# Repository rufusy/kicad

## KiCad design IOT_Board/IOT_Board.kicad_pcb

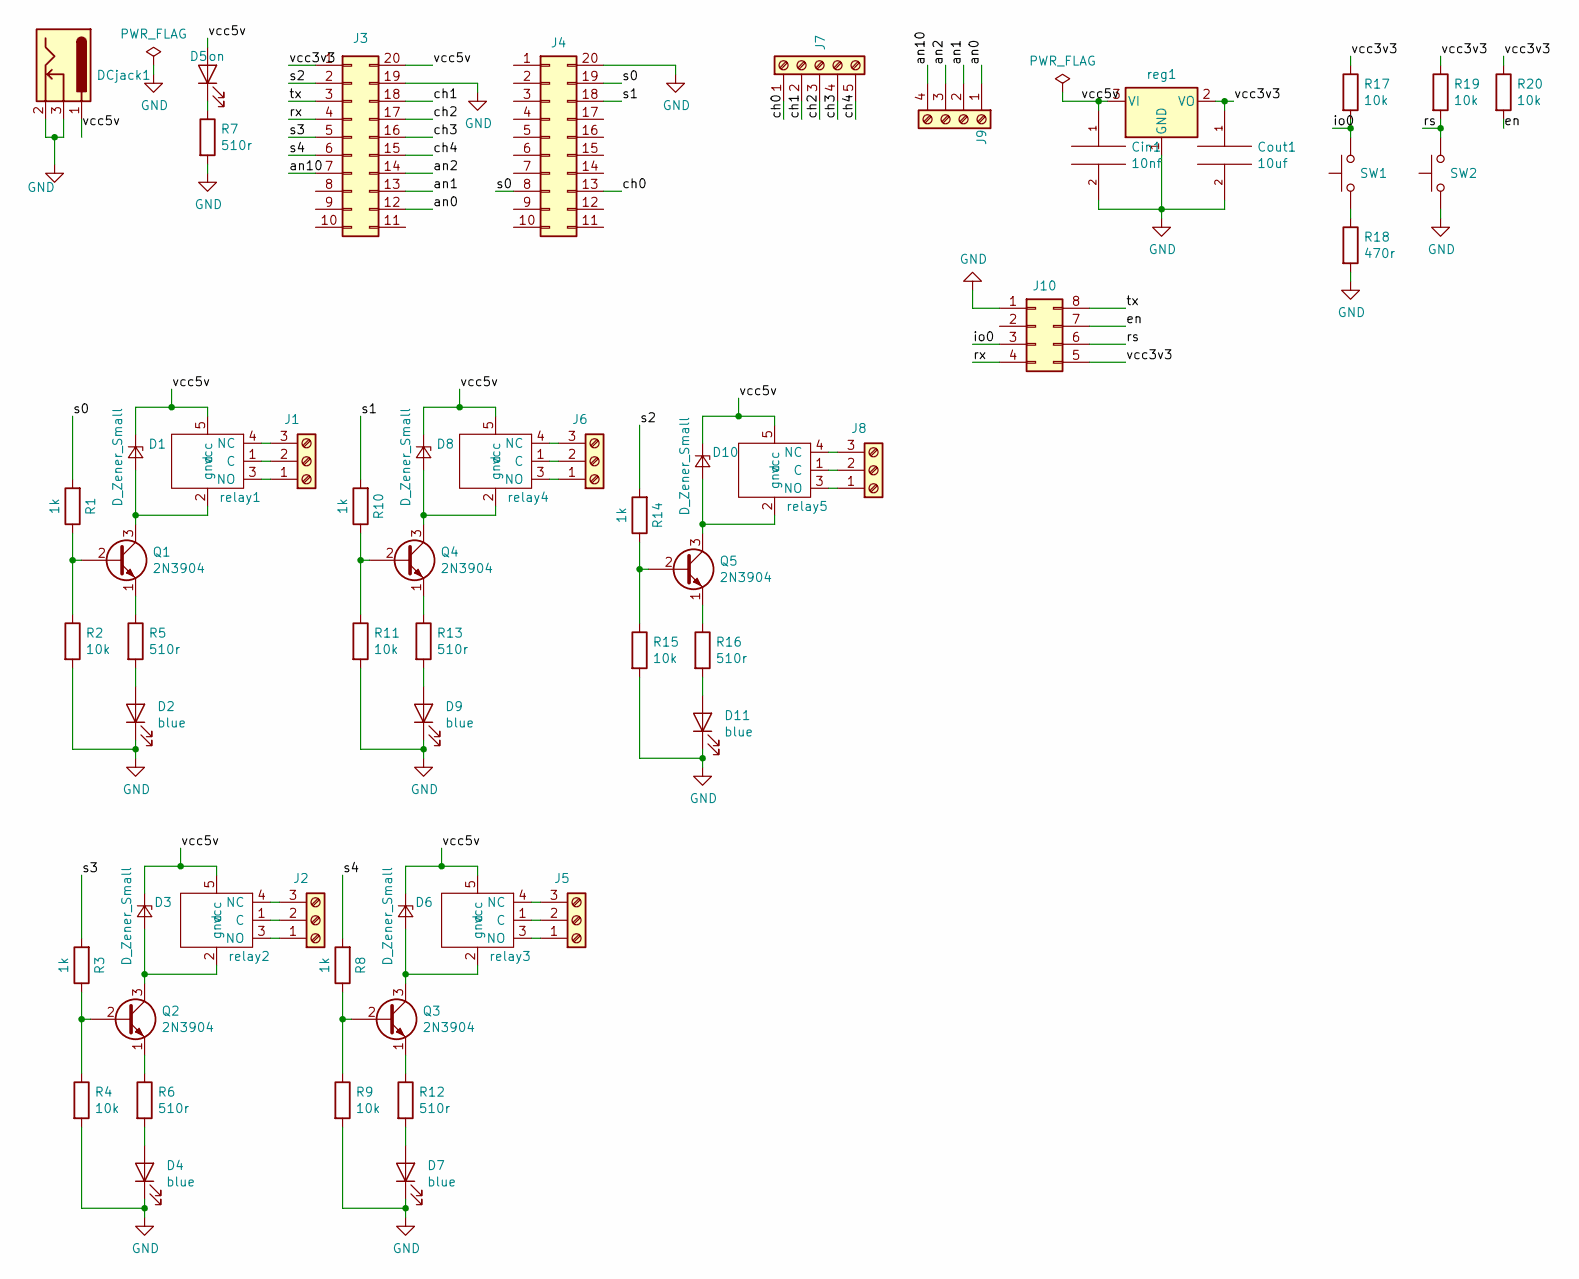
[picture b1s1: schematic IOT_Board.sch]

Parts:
Cin1: 10nf; CP_Radial_D4.0mm_P1.50mm
Cout1: 10uf; CP_Radial_D4.0mm_P1.50mm
D1, D3, D6, D8, D10: D_Zener_Small; D_A-405_P7.62mm_Horizontal
D2, D4, D7, D9, D11: blue; LED_D3.0mm
D5: on; LED_D3.0mm
DCjack1: Barrel_Jack_Switch; BarrelJack_Horizontal
J1, J2, J5, J6, J8: Screw_Terminal_01x03; TerminalBlock_4Ucon_1x03_P3.50mm_Horizontal
J3, J4: Conn_02x10_Counter_Clockwise; PinHeader_2x10_P1.00mm_Vertical
J7: Screw_Terminal_01x05; TerminalBlock_4Ucon_1x05_P3.50mm_Horizontal
J9: Screw_Terminal_01x04; TerminalBlock_4Ucon_1x04_P3.50mm_Horizontal
J10: Conn_02x04_Counter_Clockwise; PinHeader_2x04_P1.00mm_Vertical
Q1, Q2, Q3, Q4, Q5: 2N3904; TO-92_Inline
R1, R3, R8, R10, R14: 1k; R_Axial_DIN0204_L3.6mm_D1.6mm_P5.08mm_Horizontal
R2, R4, R9, R11, R15, R17, R19, R20: 10k; R_Axial_DIN0204_L3.6mm_D1.6mm_P5.08mm_Horizontal
R5, R6, R7, R12, R13, R16: 510r; R_Axial_DIN0204_L3.6mm_D1.6mm_P5.08mm_Horizontal
R18: 470r; R_Axial_DIN0204_L3.6mm_D1.6mm_P5.08mm_Horizontal
SW1, SW2: SW_Push; SW_PUSH_6mm_H13mm
reg1: LD1117S33TR_SOT223; TO-3P-3_Vertical
relay1, relay2, relay3, relay4, relay5: 5V_DC_Relay_Switch; Relay_SPDT_SANYOU_SRD_Series_Form_C

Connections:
/an0: J3.12, J9.1
/an1: J3.13, J9.2
/an2: J3.14, J9.3
/an10: J3.7, J9.4
/ch0: J4.13, J7.1
/ch1: J3.18, J7.2
/ch2: J3.17, J7.3
/ch3: J3.16, J7.4
/ch4: J3.15, J7.5
/en: J10.7, R20.2
/io0: J10.3, R17.2, SW1.2
/rs: J10.6, R19.2, SW2.2
/rx: J3.4, J10.4
/s0: J4.8, J4.19, R1.2
/s1: J4.18, R10.2
/s2: J3.2, R14.2
/s3: J3.5, R3.2
/s4: J3.6, R8.2
/tx: J3.3, J10.8
/vcc3v3: Cout1.1, J3.1, J10.5, R17.1, R19.1, R20.1, reg1.2 (VO)
/vcc5v: Cin1.1, D1.1 (K), D3.1 (K), D5.2 (A), D6.1 (K), D8.1 (K), D10.1 (K), DCjack1.1, J3.20, reg1.3 (VI), relay1.5 (vcc), relay2.5 (vcc), relay3.5 (vcc), relay4.5 (vcc), relay5.5 (vcc)
GND: Cin1.2, Cout1.2, D2.1 (K), D4.1 (K), D7.1 (K), D9.1 (K), D11.1 (K), DCjack1.2, DCjack1.3, J3.19, J4.20, J10.1, R2.2, R4.2, R7.2, R9.2, R11.2, R15.2, R18.2, SW2.1, reg1.1 (GND)
unnamed: D1.2 (A), Q1.3 (C), relay1.2 (gnd)
unnamed: D2.2 (A), R5.2
unnamed: D3.2 (A), Q2.3 (C), relay2.2 (gnd)
unnamed: D4.2 (A), R6.2
unnamed: D5.1 (K), R7.1
unnamed: D6.2 (A), Q3.3 (C), relay3.2 (gnd)
unnamed: D7.2 (A), R12.2
unnamed: D8.2 (A), Q4.3 (C), relay4.2 (gnd)
unnamed: D9.2 (A), R13.2
unnamed: D10.2 (A), Q5.3 (C), relay5.2 (gnd)
unnamed: D11.2 (A), R16.2
unnamed: J1.1, relay1.3 (NO)
unnamed: J1.2, relay1.1 (C)
unnamed: J1.3, relay1.4 (NC)
unnamed: J2.1, relay2.3 (NO)
unnamed: J2.2, relay2.1 (C)
unnamed: J2.3, relay2.4 (NC)
unnamed: J5.1, relay3.3 (NO)
unnamed: J5.2, relay3.1 (C)
unnamed: J5.3, relay3.4 (NC)
unnamed: J6.1, relay4.3 (NO)
unnamed: J6.2, relay4.1 (C)
unnamed: J6.3, relay4.4 (NC)
unnamed: J8.1, relay5.3 (NO)
unnamed: J8.2, relay5.1 (C)
unnamed: J8.3, relay5.4 (NC)
unnamed: Q1.1 (E), R5.1
unnamed: Q1.2 (B), R1.1, R2.1
unnamed: Q2.1 (E), R6.1
unnamed: Q2.2 (B), R3.1, R4.1
unnamed: Q3.1 (E), R12.1
unnamed: Q3.2 (B), R8.1, R9.1
unnamed: Q4.1 (E), R13.1
unnamed: Q4.2 (B), R10.1, R11.1
unnamed: Q5.1 (E), R16.1
unnamed: Q5.2 (B), R14.1, R15.1
unnamed: R18.1, SW1.1

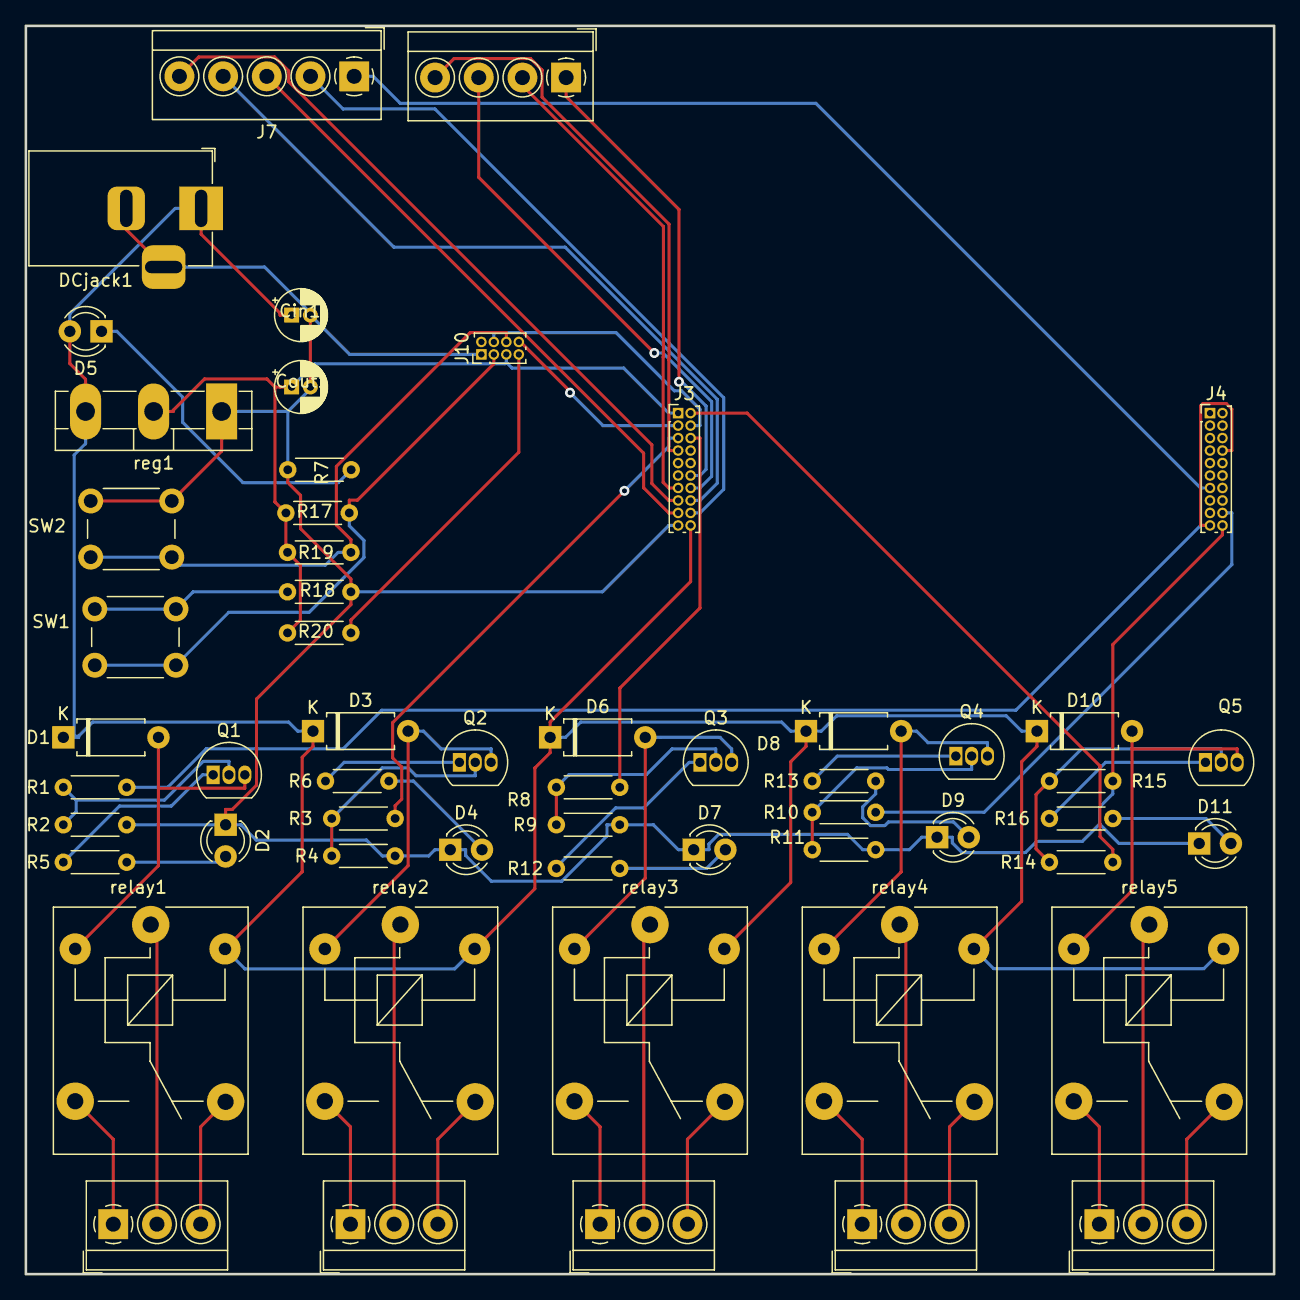
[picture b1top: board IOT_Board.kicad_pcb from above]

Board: 2 copper layers, 100.0 x 100.0 mm, 57 parts (0 on the bottom side), 59 nets.

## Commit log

2019-05-16 associated footprints, layed out PCB
2019-05-16 layout for TIVA board
2019-05-19 added tracks, produced gerber files
